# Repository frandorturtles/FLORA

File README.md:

# FLORA — Smart Plant Companion  🌸

🇬🇧 **[Read this in English → README.en.md](README.en.md)**

**Autora:** Francesca Emilsen Martínez · [@frandorturtles](https://github.com/frandorturtles) · 

Monitor de plantas con **ESP32-C3** en una **PCB con forma de flor** (5 pétalos, 56,5 × 53 mm, 2 capas, 2 orificios de montaje M2, firma «frandorturtles» en la serigrafía).
Mide humedad del suelo (sonda capacitiva), temperatura y humedad del aire (SHT40) y luz (TSL25911), y lo muestra en una pantalla OLED con LEDs de estado y alerta sonora opcional. Alimentación por USB-C (5 V).

> **Estado honesto (v0.2): diseño completo y verificado con herramientas automáticas, pero SIN fabricar y SIN probar en hardware.**
> Los colores de las imágenes son de presentación; el color real de la máscara depende del fabricante.

## Qué hay en este repositorio
| Carpeta | Contenido |
|---|---|
| `hardware/` | Proyecto KiCad (`FLORA.kicad_pro/.kicad_sch/.kicad_pcb`), símbolo propio, BOM, pinout, Gerbers, taladros, posiciones, scripts generadores |
| `firmware/` | Firmware ESP32-C3 (Arduino/PlatformIO), lógica probada en PC y comprobación de sintaxis |
| `documentation/` | Arquitectura, diseño eléctrico, montaje, plan de pruebas, BOM, ERC, revisión de diseño |
| `manufacturing/` | Notas de fabricación, ensamblaje, checklist y el ZIP de Gerbers |
| `renders/` | Vistas superior/inferior (desde los Gerbers), vista de fabricación y modelo STEP de la placa |
| `website/` y `docs/` | Sitio web morado de FLORA (`docs/index.html` lo sirve GitHub Pages) |
| `portfolio/` | Página de caso de estudio (ES/EN) y textos para el portafolio |

## Funciones (v0.2)
Humedad de suelo calibrable (seco/húmedo) · temperatura y HR ambiente · luz · OLED 0,96" · 3 LEDs (seco / OK / exceso) · zumbador desactivable · botón de usuario + reset · umbrales configurables · aviso de sonda desconectada · 10 puntos de prueba · USB-C 5 V (sin PD) · 2 orificios M2 · **sin riego automático, sin batería**.

## Verificaciones
| Comprobación | Estado |
|---|---|
| Netlist del esquemático = modelo de diseño | ✅ automática (`check_netlist.py`) |
| ERC propio sobre el netlist (tipos de pin, alimentaciones, pines vs huellas) | ✅ 0 errores, 0 avisos — (`documentation/erc_report.md`) |
| ERC oficial de KiCad |
| DRC de la PCB (KiCad 7.0.11, **sobre el mismo archivo entregado**) | ✅ 0 errores, 0 pads sin conectar. Quedan avisos "librería no configurada" (ejecución sin tabla de librerías) y 1 aviso de serigrafía |
| Gerbers del mismo archivo, leídos con un visor independiente (gerbonara) y revisados visualmente | ✅ |
| Lógica del firmware (pruebas en PC, g++) | ✅ |
| Firmware: sintaxis y tipos contra cabeceras simuladas de Arduino | ✅ (`firmware/test/syntax_check.sh`) |
| Pines contrastados con hoja de datos | ✅ ESP32-C3-WROOM-02, TSL25911FN, AP2112K, USBLC6-2SC6, SMF5.0CA · ⚠️ SHT40, AO3401A, 2N7002, USB-C, zumbador: solo símbolos oficiales de KiCad |
| Fabricación, ensamblaje, pruebas físicas | ❌ pendientes (`documentation/testing_plan.md`) |

Lista completa de limitaciones: `documentation/design_review.md`.

## Cómo empezar
1. **Abrir:** `hardware/FLORA.kicad_pro` en KiCad 10 (los archivos están en formato KiCad 7; KiCad 10 los actualiza al guardar). Ejecuta ERC y DRC.
2. **Fabricar:** `manufacturing/fabrication_notes.md` y `manufacturing/FLORA_gerbers_for_fab.zip` (vuelve a trazar desde KiCad 10 si prefieres, ver `gerber_checklist.md`).
3. **Comprar:** `hardware/bom.csv` (verifica stock y números de parte).
4. **Montar:** `documentation/assembly_guide.md`.
5. **Firmware:** `firmware/README.md`.
6. **Probar:** `documentation/testing_plan.md`.

## Regenerar el hardware desde cero
Ver `hardware/scripts/README.md`.

## Licencia
MIT (ver `LICENSE`). Puedes cambiar la licencia del hardware (por ejemplo CERN-OHL-P o CC BY 4.0).

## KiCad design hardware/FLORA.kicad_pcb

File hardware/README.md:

# Hardware — FLORA

Abre `FLORA.kicad_pro` con **KiCad 10** (los archivos `.kicad_sch` y `.kicad_pcb` están en formato KiCad 7 y se actualizan al guardar). Contenido: esquemático, placa rutada, símbolo del módulo ESP32-C3-WROOM-02 (`FLORA.kicad_sym` + `sym-lib-table`), `bom.csv`, `pinout.csv`, `gerbers/`, `drill/`, `assembly/FLORA_pos.csv`.

Primer paso recomendado: ERC (esquemático) y DRC (PCB) en KiCad.

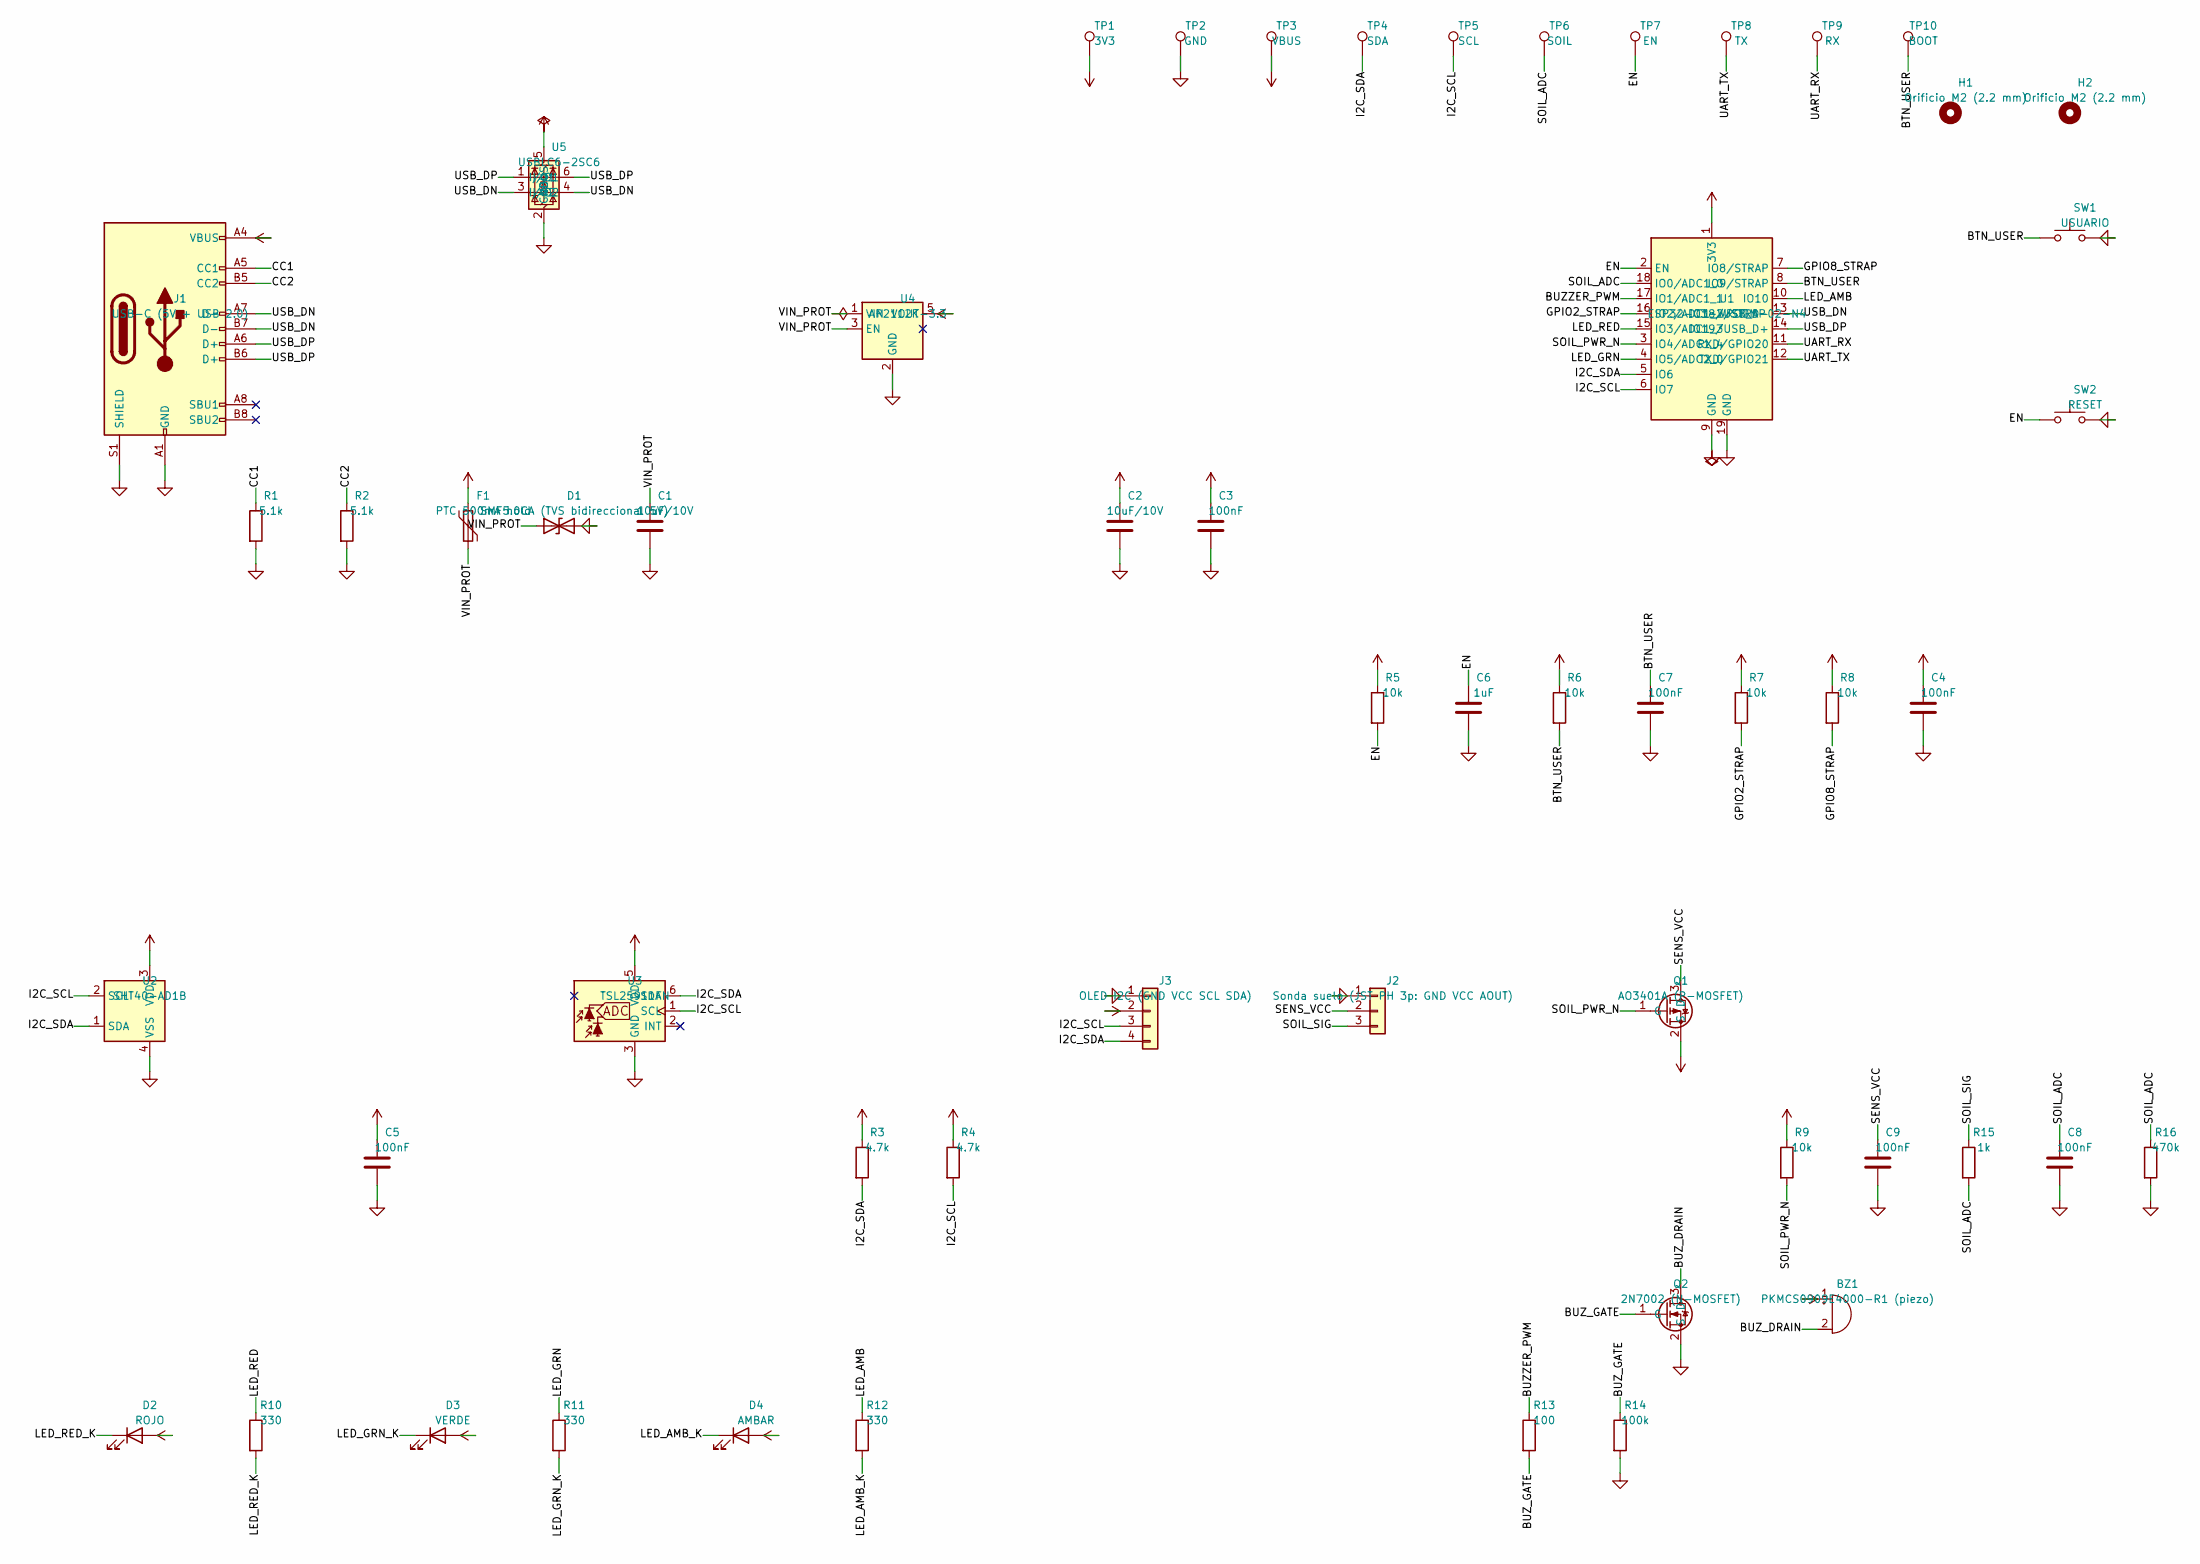
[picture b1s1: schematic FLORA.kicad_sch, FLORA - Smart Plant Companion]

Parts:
BZ1: PKMCS0909E4000-R1 (piezo); Buzzer_Murata_PKMCS0909E; MPN Murata PKMCS0909E4000-R1
C1, C2: 10uF/10V; C_0805_2012Metric; MPN Samsung CL21A106KPFNNNE
C3, C4, C5, C7, C8, C9: 100nF; C_0603_1608Metric; MPN Samsung CL10B104KB8NNNC
C6: 1uF; C_0603_1608Metric; MPN Samsung CL10A105KB8NNNC
D1: SMF5.0CA (TVS bidireccional 5V); D_SOD-123F; MPN Littelfuse SMF5.0CA (SOD-123FL; bidirec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
D2: ROJO; LED_0603_1608Metric; MPN LED 0603 rojo
D3: VERDE; LED_0603_1608Metric; MPN LED 0603 verde
D4: AMBAR; LED_0603_1608Metric; MPN LED 0603 ambar
F1: PTC 500mA hold; Fuse_1206_3216Metric; MPN Bourns MF-MSMF050-2 (o equivalente)
H1, H2: Orificio M2 (2.2 mm); MountingHole_2.2mm_M2; MPN Sin componente
J1: USB-C (5V + USB 2.0); USB_C_Receptacle_GCT_USB4105-xx-A_16P_TopMnt_Horizontal; MPN GCT USB4105-GF-A
J2: Sonda suelo (JST PH 3p: GND VCC AOUT); JST_PH_B3B-PH-K_1x03_P2.00mm_Vertical; MPN JST B3B-PH-K-S
J3: OLED I2C (GND VCC SCL SDA); PinSocket_1x04_P2.54mm_Vertical; MPN Socket hembra 1x4 2.54mm
Q1: AO3401A (P-MOSFET); SOT-23; MPN Alpha&Omega AO3401A
Q2: 2N7002 (N-MOSFET); SOT-23; MPN 2N7002 (onsemi/Nexperia)
R1, R2: 5.1k; R_0603_1608Metric; MPN Yageo RC0603FR-075K1L
R3, R4: 4.7k; R_0603_1608Metric; MPN Yageo RC0603FR-074K7L
R5, R6, R7, R8, R9: 10k; R_0603_1608Metric; MPN Yageo RC0603FR-0710KL
R10, R11, R12: 330; R_0603_1608Metric; MPN Yageo RC0603FR-07330RL
R13: 100; R_0603_1608Metric; MPN Yageo RC0603FR-07100RL
R14: 100k; R_0603_1608Metric; MPN Yageo RC0603FR-07100KL
R15: 1k; R_0603_1608Metric; MPN Yageo RC0603FR-071KL
R16: 470k; R_0603_1608Metric; MPN Yageo RC0603FR-07470KL
SW1: USUARIO; SW_Push_1P1T_NO_CK_KMR2; MPN C&K KMR2 (o equivalente)
SW2: RESET; SW_Push_1P1T_NO_CK_KMR2; MPN C&K KMR2 (o equivalente)
TP1: 3V3; TestPoint_Pad_D1.5mm; MPN Pad de prueba
TP2: GND; TestPoint_Pad_D1.5mm; MPN Pad de prueba
TP3: VBUS; TestPoint_Pad_D1.5mm; MPN Pad de prueba
TP4: SDA; TestPoint_Pad_D1.5mm; MPN Pad de prueba
TP5: SCL; TestPoint_Pad_D1.5mm; MPN Pad de prueba
TP6: SOIL; TestPoint_Pad_D1.5mm; MPN Pad de prueba
TP7: EN; TestPoint_Pad_D1.5mm; MPN Pad de prueba
TP8: TX; TestPoint_Pad_D1.5mm; MPN Pad de prueba
TP9: RX; TestPoint_Pad_D1.5mm; MPN Pad de prueba
TP10: BOOT; TestPoint_Pad_D1.5mm; MPN Pad de prueba
U1: ESP32-C3-WROOM-02-N4; ESP32-C3-WROOM-02; MPN Espressif ESP32-C3-WROOM-02-N4
U2: SHT40-AD1B; Sensirion_DFN-4_1.5x1.5mm_P0.8mm_SHT4x_NoCentralPad; MPN Sensirion SHT40-AD1B-R2
U3: TSL25911FN; AMS_TSL25911FN; MPN ams-OSRAM TSL25911FN
U4: AP2112K-3.3; SOT-23-5; MPN Diodes Inc. AP2112K-3.3TRG1
U5: USBLC6-2SC6; SOT-23-6; MPN STMicroelectronics USBLC6-2SC6

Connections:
+3V3: BZ1.1 (+), C2.1, C3.1, C4.1, C5.1, D2.2 (A), D3.2 (A), D4.2 (A), J3.2, Q1.2 (S), R3.1, R4.1, R5.1, R6.1, R7.1, R8.1, R9.1, TP1.1, U1.1 (3V3), U2.3 (VDD), U3.5 (VDD), U4.5 (VOUT)
/BTN_USER: C7.1, R6.2, SW1.1, TP10.1, U1.8 (IO9/STRAP)
/BUZZER_PWM: R13.1, U1.17 (IO1/ADC1_1)
/BUZ_DRAIN: BZ1.2 (-), Q2.3 (D)
/BUZ_GATE: Q2.1 (G), R13.2, R14.1
/CC1: J1.A5 (CC1), R1.1
/CC2: J1.B5 (CC2), R2.1
/EN: C6.1, R5.2, SW2.1, TP7.1, U1.2 (EN)
/GPIO2_STRAP: R7.2, U1.16 (IO2/ADC1_2/STRAP)
/GPIO8_STRAP: R8.2, U1.7 (IO8/STRAP)
/I2C_SCL: J3.3, R4.2, TP5.1, U1.6 (IO7), U2.2 (SCL), U3.1 (SCL)
/I2C_SDA: J3.4, R3.2, TP4.1, U1.5 (IO6), U2.1 (SDA), U3.6 (SDA)
/LED_AMB: R12.1, U1.10 (IO10)
/LED_AMB_K: D4.1 (K), R12.2
/LED_GRN: R11.1, U1.4 (IO5/ADC2_0)
/LED_GRN_K: D3.1 (K), R11.2
/LED_RED: R10.1, U1.15 (IO3/ADC1_3)
/LED_RED_K: D2.1 (K), R10.2
/SENS_VCC: C9.1, J2.2, Q1.3 (D)
/SOIL_ADC: C8.1, R15.2, R16.1, TP6.1, U1.18 (IO0/ADC1_0)
/SOIL_PWR_N: Q1.1 (G), R9.2, U1.3 (IO4/ADC1_4)
/SOIL_SIG: J2.3, R15.1
/UART_RX: TP9.1, U1.11 (RXD/GPIO20)
/UART_TX: TP8.1, U1.12 (TXD/GPIO21)
/USB_DN: J1.A7 (D-), J1.B7 (D-), U1.13 (IO18/USB_D-), U5.3 (I/O2), U5.4 (I/O2)
/USB_DP: J1.A6 (D+), J1.B6 (D+), U1.14 (IO19/USB_D+), U5.1 (I/O1), U5.6 (I/O1)
/VIN_PROT: C1.1, D1.1 (A1), F1.2, U4.1 (VIN), U4.3 (EN)
GND: C1.2, C2.2, C3.2, C4.2, C5.2, C6.2, C7.2, C8.2, C9.2, D1.2 (A2), J1.A1 (GND), J1.A12 (GND), J1.B1 (GND), J1.B12 (GND), J1.S1 (SHIELD), J2.1, J3.1, Q2.2 (S), R1.2, R2.2, R14.2, R16.2, SW1.2, SW2.2, TP2.1, U1.9 (GND), U1.19 (GND), U2.4 (VSS), U3.3 (GND), U4.2 (GND), U5.2 (GND)
VBUS: F1.1, J1.A4 (VBUS), J1.A9 (VBUS), J1.B4 (VBUS), J1.B9 (VBUS), TP3.1, U5.5 (VBUS)

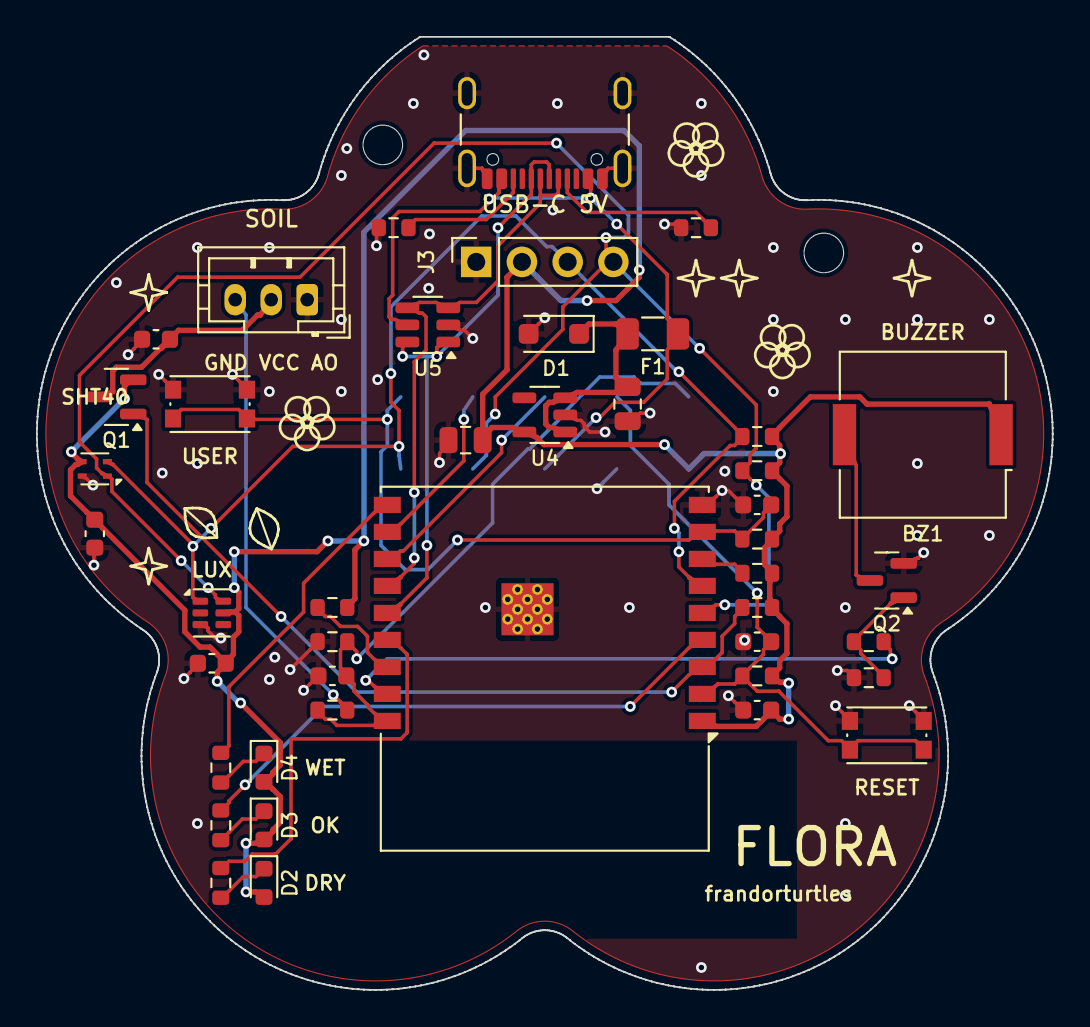
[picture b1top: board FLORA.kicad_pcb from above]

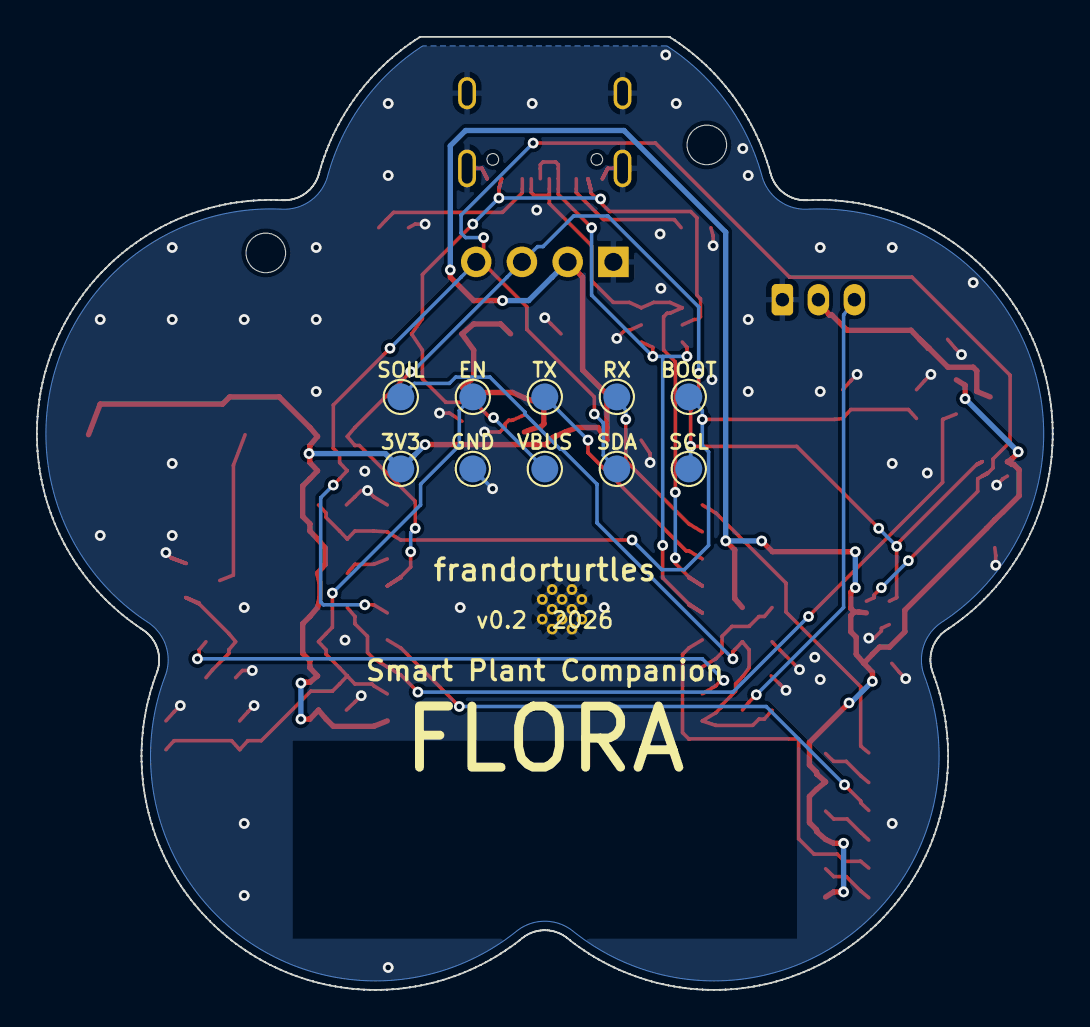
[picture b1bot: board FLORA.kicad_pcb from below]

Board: 2 copper layers, 56.4 x 52.9 mm, 55 parts (10 on the bottom side), 29 nets.

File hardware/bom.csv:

Referencias,Cantidad,Valor / descripcion,Huella KiCad,Fabricante / MPN (SIN verificar stock),Alternativas compatibles (a verificar)
U1,1,ESP32-C3-WROOM-02-N4,RF_Module:ESP32-C3-WROOM-02,Espressif ESP32-C3-WROOM-02-N4,"ESP32-C3-WROOM-02U-N4 (conector u.FL, otra huella de antena); ESP32-C3-MINI-1 (otra huella, no incluida en KiCad 7)"
U2,1,SHT40-AD1B,Sensor_Humidity:Sensirion_DFN-4_1.5x1.5mm_P0.8mm_SHT4x_NoCentralPad,Sensirion SHT40-AD1B-R2,"SHT41/SHT45 (misma huella DFN-4, mayor precision); SHT31-DIS (otra huella)"
U3,1,TSL25911FN,OptoDevice:AMS_TSL25911FN,ams-OSRAM TSL25911FN,"TSL2591 (mismo mapa de registros, otra huella); BH1750FVI (otra huella WSOF6I, direccion 0x23)"
U4,1,AP2112K-3.3,Package_TO_SOT_SMD:SOT-23-5,Diodes Inc. AP2112K-3.3TRG1,ME6211C33 / XC6220B331 / MIC5504-3.3 (SOT-23-5; verificar patillaje)
U5,1,USBLC6-2SC6,Package_TO_SOT_SMD:SOT-23-6,STMicroelectronics USBLC6-2SC6,PRTR5V0U2X (otra huella SOT-143B)
J1,1,USB-C (5V + USB 2.0),Connector_USB:USB_C_Receptacle_GCT_USB4105-xx-A_16P_TopMnt_Horizontal,GCT USB4105-GF-A,
F1,1,PTC 500mA hold,Fuse:Fuse_1206_3216Metric,Bourns MF-MSMF050-2 (o equivalente),
D1,1,SMF5.0CA (TVS bidireccional 5V),Diode_SMD:D_SOD-123F,"Littelfuse SMF5.0CA (SOD-123FL; bidireccional, VRWM 5 V, VBR min 6.4 V, VC 9.2 V)","SMBJ5.0CA (SMB, otra huella); SMF5.0CA de otro fabricante (SOD-123FL)"
Q1,1,AO3401A (P-MOSFET),Package_TO_SOT_SMD:SOT-23,Alpha&Omega AO3401A,"Si2301 / DMG3415U (SOT-23, G-S-D igual: verificar)"
Q2,1,2N7002 (N-MOSFET),Package_TO_SOT_SMD:SOT-23,2N7002 (onsemi/Nexperia),BSS138 / Si2302 (SOT-23)
BZ1,1,PKMCS0909E4000-R1 (piezo),Buzzer_Beeper:Buzzer_Murata_PKMCS0909E,Murata PKMCS0909E4000-R1,Zumbador piezo SMD 9x9 mm de resonancia ~4 kHz equivalente; o no montar (BOM opcional)
J2,1,Sonda suelo (JST PH 3p: GND VCC AOUT),Connector_JST:JST_PH_B3B-PH-K_1x03_P2.00mm_Vertical,JST B3B-PH-K-S,
J3,1,OLED I2C (GND VCC SCL SDA),Connector_PinSocket_2.54mm:PinSocket_1x04_P2.54mm_Vertical,Socket hembra 1x4 2.54mm,
SW1,1,USUARIO,Button_Switch_SMD:SW_Push_1P1T_NO_CK_KMR2,C&K KMR2 (o equivalente),
SW2,1,RESET,Button_Switch_SMD:SW_Push_1P1T_NO_CK_KMR2,C&K KMR2 (o equivalente),
D2,1,ROJO,LED_SMD:LED_0603_1608Metric,LED 0603 rojo,
D3,1,VERDE,LED_SMD:LED_0603_1608Metric,LED 0603 verde,
D4,1,AMBAR,LED_SMD:LED_0603_1608Metric,LED 0603 ambar,
R1 R2,2,5.1k,Resistor_SMD:R_0603_1608Metric,Yageo RC0603FR-075K1L,
R3 R4,2,4.7k,Resistor_SMD:R_0603_1608Metric,Yageo RC0603FR-074K7L,
R5 R6 R7 R8 R9,5,10k,Resistor_SMD:R_0603_1608Metric,Yageo RC0603FR-0710KL,
R10 R11 R12,3,330,Resistor_SMD:R_0603_1608Metric,Yageo RC0603FR-07330RL,
R13,1,100,Resistor_SMD:R_0603_1608Metric,Yageo RC0603FR-07100RL,
R14,1,100k,Resistor_SMD:R_0603_1608Metric,Yageo RC0603FR-07100KL,
R15,1,1k,Resistor_SMD:R_0603_1608Metric,Yageo RC0603FR-071KL,
R16,1,470k,Resistor_SMD:R_0603_1608Metric,Yageo RC0603FR-07470KL,
C1 C2,2,10uF/10V,Capacitor_SMD:C_0805_2012Metric,Samsung CL21A106KPFNNNE,
C3 C4 C5 C7 C8 C9,6,100nF,Capacitor_SMD:C_0603_1608Metric,Samsung CL10B104KB8NNNC,
C6,1,1uF,Capacitor_SMD:C_0603_1608Metric,Samsung CL10A105KB8NNNC,
H1 H2,2,Orificio M2 (2.2 mm),MountingHole:MountingHole_2.2mm_M2,Sin componente,
TP1,1,3V3,TestPoint:TestPoint_Pad_D1.5mm,Pad de prueba,
TP2,1,GND,TestPoint:TestPoint_Pad_D1.5mm,Pad de prueba,
TP3,1,VBUS,TestPoint:TestPoint_Pad_D1.5mm,Pad de prueba,
TP4,1,SDA,TestPoint:TestPoint_Pad_D1.5mm,Pad de prueba,
TP5,1,SCL,TestPoint:TestPoint_Pad_D1.5mm,Pad de prueba,
TP6,1,SOIL,TestPoint:TestPoint_Pad_D1.5mm,Pad de prueba,
TP7,1,EN,TestPoint:TestPoint_Pad_D1.5mm,Pad de prueba,
TP8,1,TX,TestPoint:TestPoint_Pad_D1.5mm,Pad de prueba,
TP9,1,RX,TestPoint:TestPoint_Pad_D1.5mm,Pad de prueba,
TP10,1,BOOT,TestPoint:TestPoint_Pad_D1.5mm,Pad de prueba,

NO EN PCB (comprar aparte),1,"Modulo OLED SSD1306 0.96in I2C 128x64, orden de pines GND-VCC-SCL-SDA",Cabezal macho 4 pines,Generico (verificar orden de pines VCC/GND: varia segun fabricante),
NO EN PCB (comprar aparte),1,Sonda de humedad de suelo capacitiva (tipo v1.2) con cable JST-PH 3 pines GND-VCC-AOUT,-,Generico (calidad muy variable; ver testing_plan.md),

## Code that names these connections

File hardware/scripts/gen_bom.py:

#!/usr/bin/env python3
"""Genera bom.csv, pinout.csv y la tabla de componentes de ensamblaje desde flora_data.py."""
import csv, os, sys
from collections import OrderedDict
sys.path.insert(0, os.path.dirname(__file__)); import flora_data as D
HW = os.environ.get("FLORA_HW", os.path.abspath(os.path.join(os.path.dirname(__file__), "..")))
ALT = {
 "ESP32-C3-WROOM-02-N4": "ESP32-C3-WROOM-02U-N4 (conector u.FL, otra huella de antena); ESP32-C3-MINI-1 (otra huella, no incluida en KiCad 7)",
 "SHT40-AD1B": "SHT41/SHT45 (misma huella DFN-4, mayor precision); SHT31-DIS (otra huella)",
 "TSL25911FN": "TSL2591 (mismo mapa de registros, otra huella); BH1750FVI (otra huella WSOF6I, direccion 0x23)",
 "AP2112K-3.3": "ME6211C33 / XC6220B331 / MIC5504-3.3 (SOT-23-5; verificar patillaje)",
 "USBLC6-2SC6": "PRTR5V0U2X (otra huella SOT-143B)", "SMF5.0CA (TVS bidireccional 5V)": "SMBJ5.0CA (SMB, otra huella); SMF5.0CA de otro fabricante (SOD-123FL)", "AO3401A (P-MOSFET)": "Si2301 / DMG3415U (SOT-23, G-S-D igual: verificar)",
 "2N7002 (N-MOSFET)": "BSS138 / Si2302 (SOT-23)", "PKMCS0909E4000-R1 (piezo)": "Zumbador piezo SMD 9x9 mm de resonancia ~4 kHz equivalente; o no montar (BOM opcional)",
}
rows = OrderedDict()
for ref, lib, val, fp, mpn, nets in D.PARTS:
    key = (val, fp, mpn)
    rows.setdefault(key, []).append(ref)
def natkey(r): 
    import re; m = re.match(r"([A-Z]+)(\d+)", r); return (m.group(1), int(m.group(2)))
with open(os.path.join(HW, "bom.csv"), "w", newline="") as f:
    w = csv.writer(f); w.writerow(["Referencias", "Cantidad", "Valor / descripcion", "Huella KiCad", "Fabricante / MPN (SIN verificar stock)", "Alternativas compatibles (a verificar)"])
    for (val, fp, mpn), refs in rows.items():
        refs = sorted(refs, key=natkey)
        w.writerow([" ".join(refs), len(refs), val, fp, mpn, ALT.get(val, "")])
    w.writerow([]); w.writerow(["NO EN PCB (comprar aparte)", 1, "Modulo OLED SSD1306 0.96in I2C 128x64, orden de pines GND-VCC-SCL-SDA", "Cabezal macho 4 pines", "Generico (verificar orden de pines VCC/GND: varia segun fabricante)", ""])
    w.writerow(["NO EN PCB (comprar aparte)", 1, "Sonda de humedad de suelo capacitiva (tipo v1.2) con cable JST-PH 3 pines GND-VCC-AOUT", "-", "Generico (calidad muy variable; ver testing_plan.md)", ""])
print("bom.csv:", sum(len(r) for r in rows.values()), "refs,", len(rows), "lineas")
# pinout
GPIO = {"1":"3V3","2":"EN","3":"GPIO4","4":"GPIO5","5":"GPIO6","6":"GPIO7","7":"GPIO8","8":"GPIO9","9":"GND","10":"GPIO10","11":"GPIO20 (RXD)","12":"GPIO21 (TXD)",
        "13":"GPIO18","14":"GPIO19","15":"GPIO3","16":"GPIO2","17":"GPIO1","18":"GPIO0","19":"GND (EPAD)"}
NOTE = {"SOIL_ADC":"ADC1_CH0; RC 1k+100nF; pull-down 470k (deteccion de sonda desconectada)","SOIL_PWR_N":"ACTIVO BAJO; gate del P-MOSFET Q1; pull-up 10k","LED_GRN":"ACTIVO BAJO (anodo a 3V3)",
        "LED_RED":"ACTIVO BAJO (anodo a 3V3)","LED_AMB":"ACTIVO BAJO (anodo a 3V3)","I2C_SDA":"I2C; pull-up 4.7k; SHT40 0x44, TSL25911 0x29, OLED 0x3C","I2C_SCL":"I2C; pull-up 4.7k",
        "BTN_USER":"Boton a GND; pull-up 10k; pin de strapping BOOT (GPIO9)","GPIO8_STRAP":"Strapping: pull-up 10k (necesario para modo descarga); sin uso","GPIO2_STRAP":"Strapping: pull-up 10k; sin uso",
        "BUZZER_PWM":"PWM ~4 kHz hacia gate de Q2 (2N7002)","USB_DN":"USB D- nativo (GPIO18)","USB_DP":"USB D+ nativo (GPIO19)","UART_TX":"UART0 TXD en pad de prueba TP8","UART_RX":"UART0 RXD en pad de prueba TP9","EN":"RC 10k+1uF + pulsador RESET (SW2)"}
u1 = [p for p in D.PARTS if p[0]=="U1"][0][5]
with open(os.path.join(HW, "pinout.csv"), "w", newline="") as f:
    w = csv.writer(f); w.writerow(["Pin modulo (U1)", "Funcion GPIO", "Red", "Notas"])
    for n in sorted(u1, key=int): w.writerow([n, GPIO[n], u1[n], NOTE.get(u1[n], "")])
print("pinout.csv ok")

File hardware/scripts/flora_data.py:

"""FLORA - modelo de diseño (única fuente de verdad del esquemático).

Cada componente: ref, lib_id (símbolo KiCad), valor, huella, MPN/fabricante, {pin_número: red}.
Pines con red None se marcan No-Connect. El PCB se genera desde el netlist exportado del
esquemático (no desde este archivo), de modo que esquemático y PCB no pueden divergir.

Pines del módulo ESP32-C3-WROOM-02: datasheet v1.7, Table 3-1 (consultado el 2026-10-25).
Pines de SHT4x, TSL25911FN, AP2112K, USBLC6-2SC6, AO3401A, 2N7002, USB-C: símbolos oficiales de
KiCad 7.0.11 (pendiente de contraste con la hoja de datos de cada fabricante: ver design_review.md).
"""
GND, V33, VBUS, VSW = "GND", "+3V3", "VBUS", "SENS_VCC"

# (n, nombre, tipo) - datasheet ESP32-C3-WROOM-02 v1.7, Table 3-1
ESP32_PINS = [
    ("1", "3V3", "power_in"), ("2", "EN", "input"), ("3", "IO4", "bidirectional"),
    ("4", "IO5", "bidirectional"), ("5", "IO6", "bidirectional"), ("6", "IO7", "bidirectional"),
    ("7", "IO8", "bidirectional"), ("8", "IO9", "bidirectional"), ("9", "GND", "power_in"),
    ("10", "IO10", "bidirectional"), ("11", "RXD", "bidirectional"), ("12", "TXD", "bidirectional"),
    ("13", "IO18", "bidirectional"), ("14", "IO19", "bidirectional"), ("15", "IO3", "bidirectional"),
    ("16", "IO2", "bidirectional"), ("17", "IO1", "bidirectional"), ("18", "IO0", "bidirectional"),
    ("19", "GND", "power_in")]

R = "Resistor_SMD:R_0603_1608Metric"
C = "Capacitor_SMD:C_0603_1608Metric"
C8 = "Capacitor_SMD:C_0805_2012Metric"
L = "LED_SMD:LED_0603_1608Metric"
TP = "TestPoint:TestPoint_Pad_D1.5mm"

# ref, lib_id, valor, huella, MPN, {pin: red}
PARTS = [
    ("U1", "FLORA:ESP32-C3-WROOM-02", "ESP32-C3-WROOM-02-N4", "RF_Module:ESP32-C3-WROOM-02",
     "Espressif ESP32-C3-WROOM-02-N4",
     {"1": V33, "2": "EN", "3": "SOIL_PWR_N", "4": "LED_GRN", "5": "I2C_SDA", "6": "I2C_SCL",
      "7": "GPIO8_STRAP", "8": "BTN_USER", "9": GND, "10": "LED_AMB", "11": "UART_RX",
      "12": "UART_TX", "13": "USB_DN", "14": "USB_DP", "15": "LED_RED", "16": "GPIO2_STRAP",
      "17": "BUZZER_PWM", "18": "SOIL_ADC", "19": GND}),
    ("U2", "Sensor_Humidity:SHT4x", "SHT40-AD1B", "Sensor_Humidity:Sensirion_DFN-4_1.5x1.5mm_P0.8mm_SHT4x_NoCentralPad",
     "Sensirion SHT40-AD1B-R2", {"1": "I2C_SDA", "2": "I2C_SCL", "3": V33, "4": GND}),
    ("U3", "Sensor_Optical:TSL25911FN", "TSL25911FN", "OptoDevice:AMS_TSL25911FN",
     "ams-OSRAM TSL25911FN", {"1": "I2C_SCL", "2": None, "3": GND, "4": None, "5": V33, "6": "I2C_SDA"}),
    ("U4", "Regulator_Linear:AP2112K-3.3", "AP2112K-3.3", "Package_TO_SOT_SMD:SOT-23-5",
     "Diodes Inc. AP2112K-3.3TRG1", {"1": "VIN_PROT", "2": GND, "3": "VIN_PROT", "4": None, "5": V33}),
    ("U5", "Power_Protection:USBLC6-2SC6", "USBLC6-2SC6", "Package_TO_SOT_SMD:SOT-23-6",
     "STMicroelectronics USBLC6-2SC6", {"1": "USB_DP", "2": GND, "3": "USB_DN", "4": "USB_DN", "5": VBUS, "6": "USB_DP"}),
    ("J1", "Connector:USB_C_Receptacle_USB2.0_16P", "USB-C (5V + USB 2.0)",
     "Connector_USB:USB_C_Receptacle_GCT_USB4105-xx-A_16P_TopMnt_Horizontal", "GCT USB4105-GF-A",
     {"A1": GND, "A12": GND, "B1": GND, "B12": GND, "S1": GND, "A4": VBUS, "A9": VBUS, "B4": VBUS,
      "B9": VBUS, "A5": "CC1", "B5": "CC2", "A6": "USB_DP", "B6": "USB_DP", "A7": "USB_DN",
      "B7": "USB_DN", "A8": None, "B8": None}),
    ("F1", "Device:Polyfuse", "PTC 500mA hold", "Fuse:Fuse_1206_3216Metric",
     "Bourns MF-MSMF050-2 (o equivalente)", {"1": VBUS, "2": "VIN_PROT"}),
    ("D1", "Device:D_TVS", "SMF5.0CA (TVS bidireccional 5V)", "Diode_SMD:D_SOD-123F",
     "Littelfuse SMF5.0CA (SOD-123FL; bidireccional, VRWM 5 V, VBR min 6.4 V, VC 9.2 V)", {"1": "VIN_PROT", "2": GND}),
    ("Q1", "Transistor_FET:AO3401A", "AO3401A (P-MOSFET)", "Package_TO_SOT_SMD:SOT-23",
     "Alpha&Omega AO3401A", {"1": "SOIL_PWR_N", "2": V33, "3": VSW}),
    ("Q2", "Transistor_FET:2N7002", "2N7002 (N-MOSFET)", "Package_TO_SOT_SMD:SOT-23",
     "2N7002 (onsemi/Nexperia)", {"1": "BUZ_GATE", "2": GND, "3": "BUZ_DRAIN"}),
    ("BZ1", "Device:Buzzer", "PKMCS0909E4000-R1 (piezo)", "Buzzer_Beeper:Buzzer_Murata_PKMCS0909E",
     "Murata PKMCS0909E4000-R1", {"1": V33, "2": "BUZ_DRAIN"}),
    ("J2", "Connector_Generic:Conn_01x03", "Sonda suelo (JST PH 3p: GND VCC AOUT)",
     "Connector_JST:JST_PH_B3B-PH-K_1x03_P2.00mm_Vertical", "JST B3B-PH-K-S",
     {"1": GND, "2": VSW, "3": "SOIL_SIG"}),
    ("J3", "Connector_Generic:Conn_01x04", "OLED I2C (GND VCC SCL SDA)",
     "Connector_PinSocket_2.54mm:PinSocket_1x04_P2.54mm_Vertical", "Socket hembra 1x4 2.54mm",
     {"1": GND, "2": V33, "3": "I2C_SCL", "4": "I2C_SDA"}),
    ("SW1", "Switch:SW_Push", "USUARIO", "Button_Switch_SMD:SW_Push_1P1T_NO_CK_KMR2",
     "C&K KMR2 (o equivalente)", {"1": "BTN_USER", "2": GND}),
    ("SW2", "Switch:SW_Push", "RESET", "Button_Switch_SMD:SW_Push_1P1T_NO_CK_KMR2",
     "C&K KMR2 (o equivalente)", {"1": "EN", "2": GND}),
    ("D2", "Device:LED", "ROJO", L, "LED 0603 rojo", {"1": "LED_RED_K", "2": V33}),
    ("D3", "Device:LED", "VERDE", L, "LED 0603 verde", {"1": "LED_GRN_K", "2": V33}),
    ("D4", "Device:LED", "AMBAR", L, "LED 0603 ambar", {"1": "LED_AMB_K", "2": V33}),
    # Resistencias
    ("R1", "Device:R", "5.1k", R, "Yageo RC0603FR-075K1L", {"1": "CC1", "2": GND}),
    ("R2", "Device:R", "5.1k", R, "Yageo RC0603FR-075K1L", {"1": "CC2", "2": GND}),
    ("R3", "Device:R", "4.7k", R, "Yageo RC0603FR-074K7L", {"1": V33, "2": "I2C_SDA"}),
    ("R4", "Device:R", "4.7k", R, "Yageo RC0603FR-074K7L", {"1": V33, "2": "I2C_SCL"}),
    ("R5", "Device:R", "10k", R, "Yageo RC0603FR-0710KL", {"1": V33, "2": "EN"}),
    ("R6", "Device:R", "10k", R, "Yageo RC0603FR-0710KL", {"1": V33, "2": "BTN_USER"}),
    ("R7", "Device:R", "10k", R, "Yageo RC0603FR-0710KL", {"1": V33, "2": "GPIO2_STRAP"}),
    ("R8", "Device:R", "10k", R, "Yageo RC0603FR-0710KL", {"1": V33, "2": "GPIO8_STRAP"}),
    ("R9", "Device:R", "10k", R, "Yageo RC0603FR-0710KL", {"1": V33, "2": "SOIL_PWR_N"}),
    ("R10", "Device:R", "330", R, "Yageo RC0603FR-07330RL", {"1": "LED_RED", "2": "LED_RED_K"}),
    ("R11", "Device:R", "330", R, "Yageo RC0603FR-07330RL", {"1": "LED_GRN", "2": "LED_GRN_K"}),
    ("R12", "Device:R", "330", R, "Yageo RC0603FR-07330RL", {"1": "LED_AMB", "2": "LED_AMB_K"}),
    ("R13", "Device:R", "100", R, "Yageo RC0603FR-07100RL", {"1": "BUZZER_PWM", "2": "BUZ_GATE"}),
    ("R14", "Device:R", "100k", R, "Yageo RC0603FR-07100KL", {"1": "BUZ_GATE", "2": GND}),
    ("R15", "Device:R", "1k", R, "Yageo RC0603FR-071KL", {"1": "SOIL_SIG", "2": "SOIL_ADC"}),
    ("R16", "Device:R", "470k", R, "Yageo RC0603FR-07470KL", {"1": "SOIL_ADC", "2": GND}),
    # Condensadores
    ("C1", "Device:C", "10uF/10V", C8, "Samsung CL21A106KPFNNNE", {"1": "VIN_PROT", "2": GND}),
    ("C2", "Device:C", "10uF/10V", C8, "Samsung CL21A106KPFNNNE", {"1": V33, "2": GND}),
    ("C3", "Device:C", "100nF", C, "Samsung CL10B104KB8NNNC", {"1": V33, "2": GND}),
    ("C4", "Device:C", "100nF", C, "Samsung CL10B104KB8NNNC", {"1": V33, "2": GND}),
    ("C5", "Device:C", "100nF", C, "Samsung CL10B104KB8NNNC", {"1": V33, "2": GND}),
    ("C6", "Device:C", "1uF", C, "Samsung CL10A105KB8NNNC", {"1": "EN", "2": GND}),
    ("C7", "Device:C", "100nF", C, "Samsung CL10B104KB8NNNC", {"1": "BTN_USER", "2": GND}),
    ("C8", "Device:C", "100nF", C, "Samsung CL10B104KB8NNNC", {"1": "SOIL_ADC", "2": GND}),
    ("C9", "Device:C", "100nF", C, "Samsung CL10B104KB8NNNC", {"1": VSW, "2": GND}),
    # Orificios de montaje (sin conexion electrica)
    ("H1", "Mechanical:MountingHole", "Orificio M2 (2.2 mm)", "MountingHole:MountingHole_2.2mm_M2", "Sin componente", {}),
    ("H2", "Mechanical:MountingHole", "Orificio M2 (2.2 mm)", "MountingHole:MountingHole_2.2mm_M2", "Sin componente", {}),
    # Puntos de prueba
    ("TP1", "Connector:TestPoint", "3V3", TP, "Pad de prueba", {"1": V33}),
    ("TP2", "Connector:TestPoint", "GND", TP, "Pad de prueba", {"1": GND}),
    ("TP3", "Connector:TestPoint", "VBUS", TP, "Pad de prueba", {"1": VBUS}),
    ("TP4", "Connector:TestPoint", "SDA", TP, "Pad de prueba", {"1": "I2C_SDA"}),
    ("TP5", "Connector:TestPoint", "SCL", TP, "Pad de prueba", {"1": "I2C_SCL"}),
    ("TP6", "Connector:TestPoint", "SOIL", TP, "Pad de prueba", {"1": "SOIL_ADC"}),
    ("TP7", "Connector:TestPoint", "EN", TP, "Pad de prueba", {"1": "EN"}),
    ("TP8", "Connector:TestPoint", "TX", TP, "Pad de prueba", {"1": "UART_TX"}),
    ("TP9", "Connector:TestPoint", "RX", TP, "Pad de prueba", {"1": "UART_RX"}),
    ("TP10", "Connector:TestPoint", "BOOT", TP, "Pad de prueba", {"1": "BTN_USER"}),
]

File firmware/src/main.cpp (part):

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// ESTADO: escrito para el hardware FLORA v0.1; NO compilado ni probado en placa (ver README.md).
//
// GPIO (ver hardware/pinout.csv):
//   GPIO0  SOIL_ADC   (ADC1_CH0)   salida de la sonda capacitiva, tras R 1k + C 100nF
//   GPIO4  SOIL_PWR_N              ACTIVO EN BAJO: P-MOSFET que alimenta la sonda
//   GPIO6/7 SDA/SCL                I2C: SHT40 (0x44), TSL25911 (0x29), OLED SSD1306 (0x3C)
//   GPIO9  BTN_USER                activo en bajo (pin BOOT/strapping: no pulsar durante el reset)
//   GPIO3  LED_RED, GPIO5 LED_GRN, GPIO10 LED_AMB   ACTIVOS EN BAJO (ánodo a 3V3)
//   GPIO1  BUZZER (PWM) -> 2N7002 -> zumbador piezo
#include <Arduino.h>
#include <Wire.h>
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
using namespace flora;

constexpr int PIN_SOIL_ADC = 0, PIN_SOIL_PWR_N = 4, PIN_SDA = 6, PIN_SCL = 7, PIN_BTN = 9;
constexpr int PIN_LED_RED = 3, PIN_LED_GRN = 5, PIN_LED_AMB = 10, PIN_BUZ = 1;
constexpr uint8_t ADDR_SHT = 0x44, ADDR_TSL = 0x29;

U8G2_SSD1306_128X64_NONAME_F_HW_I2C oled(U8G2_R0, U8X8_PIN_NONE);
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constexpr uint32_t SOIL_PERIOD_MS = 3000, SOIL_SETTLE_MS = 200;

float readSoilMv() {
  analogSetPinAttenuation(PIN_SOIL_ADC, ADC_11db);
  uint32_t acc = 0; for (int i = 0; i < 16; i++) acc += analogReadMilliVolts(PIN_SOIL_ADC);
  return acc / 16.0f;
}
void soilTick(uint32_t now) {
  if (soilPhase == SoilPhase::Idle && now - lastSoilCycle >= SOIL_PERIOD_MS) {
    digitalWrite(PIN_SOIL_PWR_N, LOW); soilPhase = SoilPhase::Settling; soilT0 = now;     // enciende la sonda
  } else if (soilPhase == SoilPhase::Settling && now - soilT0 >= SOIL_SETTLE_MS) {
    R.soilMv = readSoilMv();
    digitalWrite(PIN_SOIL_PWR_N, HIGH); soilPhase = SoilPhase::Idle; lastSoilCycle = now;
    R.soilOk = soilMvPlausible(R.soilMv);
    R.soilPct = R.soilOk ? soilPercent(R.soilMv, cal) : NAN;
    SoilState ns = classify(R.soilPct, R.soilOk, thr, soilState);
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    case SoilState::SensorError: r = a = ((now / 400) % 2); break;   // parpadeo rojo+ámbar
    default: g = ((now / 1000) % 2); break;                         // sin calibrar: verde lento
  }
  digitalWrite(PIN_LED_RED, r ? LOW : HIGH); digitalWrite(PIN_LED_GRN, g ? LOW : HIGH); digitalWrite(PIN_LED_AMB, a ? LOW : HIGH);
}
uint32_t beepUntil = 0;
void buzzerTone(bool on) {
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uint32_t lastEnv = 0, lastDraw = 0, lastI2cRetry = 0;
void setup() {
  Serial.begin(115200);
  pinMode(PIN_SOIL_PWR_N, OUTPUT); digitalWrite(PIN_SOIL_PWR_N, HIGH);        // sonda apagada
  pinMode(PIN_LED_RED, OUTPUT); pinMode(PIN_LED_GRN, OUTPUT); pinMode(PIN_LED_AMB, OUTPUT);
  digitalWrite(PIN_LED_RED, HIGH); digitalWrite(PIN_LED_GRN, HIGH); digitalWrite(PIN_LED_AMB, HIGH);
  pinMode(PIN_BTN, INPUT);                                                    // pull-up externo de 10k en el PCB
  buzzerInit();
  Wire.begin(PIN_SDA, PIN_SCL, 100000); Wire.setTimeOut(50);
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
